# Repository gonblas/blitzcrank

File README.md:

# Blitzcrank

<p align="center">

</p>

## Descripción del proyecto

El proyecto **Blitzcrank** es un prototipo de **garra robótica móvil** diseñado para desplazarse en dos ejes (X e Y) mediante un sistema de rieles. Sobre este plano de movimiento, la garra puede **subir, bajar, abrir y cerrar**, lo que le otorga la capacidad de manipular objetos livianos dentro de un área determinada. El control se realiza manualmente a través de un **joystick de efecto Hall** y un conjunto de botones que permiten al usuario interactuar de manera sencilla e intuitiva.

Más allá de su valor como ejercicio técnico, el prototipo puede servir como base para múltiples aplicaciones: desde la simulación de procesos de **transporte y manipulación de piezas** hasta escenarios lúdicos como las clásicas máquinas de garras o sistemas recreativos de precisión, por ejemplo, un robot capaz de jugar al ajedrez moviendo las piezas en el tablero. De esta manera, Blitzcrank demuestra cómo la **tecnología robótica** puede adaptarse tanto a la **experimentación educativa** como a la **innovación aplicada** en proyectos más complejos.

<details>
  <summary><i>Objetivos del proyecto</i></summary>

  - **Objetivos primarios:**

    Se detallan a continuación aquellos objetivos de carácter obligatorio, necesarios para la validación del proyecto.

    - Implementar un sistema de rieles que permita el desplazamiento de la garra en los ejes X e Y.
    - Incorporar un mecanismo que posibilite el movimiento vertical de la garra para subir y bajar.
    - Desarrollar un sistema de control manual que garantice un manejo sencillo e intuitivo.
    - Integrar un actuador que permita abrir y cerrar la garra para tomar y soltar objetos.

  - **Objetivos secundarios:**

    A continuación se detallan aquellos objetivos de carácter opcional, sujetos a tiempo, materiales y costos disponibles.

    - Adaptar el sistema para manipular piezas de ajedrez en un tablero, garantizando precisión en la colocación.
    - Implementar un módulo de visión artificial que permita identificar la posición de las piezas en el tablero.
    - Integrar un algoritmo de inteligencia artificial que tome decisiones de juego y guíe automáticamente los movimientos de la garra.
    - Implementar una interfaz web que permita el manejo de la garra.

</details>

<details>
  <summary><i>Requerimientos del proyecto</i></summary>

  ##### Requerimientos Funcionales

  - **Requerimientos de Hardware:**

    - Debe contar con una interfaz física para mover la garra.
      - El sistema debe incluir unos botones dedicados al ascenso y descenso de la garra.
      - El sistema debe incluir un potenciómetro dedicado a la apertura y cierre de la garra.
      - El sistema debe incorporar un controlador para manejar los movimientos de la garra en los ejes X e Y.
      - El sistema debe incorporar un botón para manejar el cambio de modo físico y remoto.
    - Movimiento preciso de la garra.
      - El sistema de rieles debe permitir el movimiento de la garra en dos ejes cartesianos (X e Y), con un área mínima de trabajo de 15 cm x 15 cm.
      - El eje Z debe recorrer verticalmente al menos 5 cm para tomar y elevar piezas.
      - Se deben utilizar motores paso a paso para garantizar la posición exacta de la garra.
      - La garra debe ser capaz de levantar objetos de 50 gramos.
    - Todos los componentes deben estar ensamblados con fines de obtener un único sistema final compacto.

  - **Requerimientos de Software:**

    - Se debe desarrollar una interfaz de usuario capaz de controlar el sistema.
      - Desarrollar una interfaz que permita controlar manualmente la garra.
      - Implementar una interfaz web que permita seleccionar el modo de operación.
      - La interfaz debe ser intuitiva y clara, mostrando el estado del sistema y los errores en caso de que ocurran.
    - El software debe gestionar los límites de movimiento, deteniendo la garra para evitar daños mecánicos.

  ##### Requerimientos no funcionales

  Estos requerimientos no afectan en la funcionalidad del proyecto, por lo cual no se ve necesidad de hacer particular énfasis en la validación, pero que sí han sido tenidos en cuenta en el desarrollo.

  - Plataforma y desarrollo.
    - Utilizar una placa EDU-CIAA-NXP como centro de control del sistema, basada en el microcontrolador NXP LPC 4337.
    - Todo el firmware del EDU-CIAA debe ser desarrollado en lenguaje C.
  - Tiempo de ejecución: 16 semanas.
  - Presupuesto total de 600.000 ARS.
  - Documentación.
    - Documentar detalladamente el proceso de ensamblado del sistema.
    - Documentar el desarrollo del firmware, incluyendo rutinas de control e inicialización.
    - Documentar el diseño del esquemático y PCB, incluyendo conexiones, componentes y disposición de pines.
  - Garantizar la seguridad del usuario durante la operación del sistema, incluyendo protecciones físicas.

</details>

<details>
  <summary><i>Diagrama en bloques del sistema</i></summary>

</details>

<details>
  <summary><i>Tecnologías utilizadas</i></summary>
  <ol>

  <li>Hardware</li>
    <ul>
      <li>EDU-CIAA-NXP (LPC4337): placa central de control del sistema</li>
      <li>ESP-WROOM-32: módulo Wi-Fi para control remoto e interfaz web</li>
      <li>Motores paso a paso Nema17: movimiento en ejes X e Y</li>
      <li>Drivers DRV8825: control de motores paso a paso</li>
      <li>Motor DC GA12N20 + Driver DRV8833: accionamiento de polea</li>
      <li>Servomotor TowerPro MG90s: apertura y cierre de la garra</li>
      <li>Joystick analógico SYSPORT: control de movimiento X-Y</li>
      <li>Potenciómetro 10k: control analógico de la garra</li>
      <li>Fuente 12V 5A + Step Down XL4005: alimentación del sistema</li>
    </ul>

  <li>Firmware</li>
    <ul>
      <li>Lenguaje C para el firmware de la EDU-CIAA-NXP</li>
      <li>C++ con Arduino Framework para el firmware del ESP32</li>
      <li>PlatformIO como entorno de desarrollo del ESP32</li>
      <li>Comunicación UART entre EDU-CIAA y ESP32</li>
    </ul>

  <li>Interfaz web (ESP32)</li>
    <ul>
      <li>HTML, CSS y JavaScript servidos desde SPIFFS</li>
      <li>ESPAsyncWebServer para el servidor web embebido</li>
      <li>WebSockets para comunicación en tiempo real</li>
    </ul>

  <li>Diseño y fabricación</li>
    <ul>
      <li><a href="https://www.kicad.org/">KiCad</a>: diseño de esquemáticos y PCB</li>
      <li><a href="https://www.autodesk.com/products/fusion-360/overview">Fusion 360</a>: modelado 3D de estructura y garra</li>
      <li><a href="https://ultimaker.com/es/software/ultimaker-cura/">UltiMaker Cura</a>: preparación de piezas para impresión 3D</li>
    </ul>

  </ol>
</details>

---

## Materiales

| Componente | Cantidad | Función |
| ---------- | -------- | ------- |
| EDU-CIAA-NXP | 1 | Placa central que coordina motores, sensores y comunicación |
| ESP-WROOM-32 38 PINES | 1 | Control inalámbrico mediante Wi-Fi, interfaz web remota |
| Potenciómetro 10k Lineal 16mm | 1 | Entrada analógica para apertura de garra |
| Push Button Tact Switch 6x6mm | 3 | Entrada digital para abrir/cerrar garra |
| Joystick analógico SYSPORT | 1 | Control principal en ejes X e Y con pulsador integrado |
| Motor DC GA12N20 | 1 | Motorreductor para accionar polea |
| Driver Motor DC Puente H DRV8833 | 1 | Control de motor DC, inversión de giro y regulación por PWM |
| Servomotor TowerPro MG90s | 1 | Apertura y cierre de la garra |
| Motor paso a paso Nema17 17HS3404N | 2 | Movimiento de ejes X-Y |
| Driver DRV8825 | 2 | Controlador de motores paso a paso |
| Fuente de 12V 5A SIMALED LCS-1721-M1 | 1 | Fuente de alimentación externa para todo el sistema |
| Módulo Step Down XL4005 | 1 | Transformador de tensión |

---

## Diseño 3D

<details>
  <summary>Sistema completo</summary>
  
</details>

<details>
  <summary>Garra</summary>
  
</details>

<details>
  <summary>Sistema de poleas</summary>
  
</details>

<details>
  <summary>Controlador</summary>

</details>

<details>
  <summary>Eje Y</summary>
  
</details>

---

## PCB

<details>
  <summary>Diseño del PCB</summary>
  
</details>

<details>
  <summary>PCB 3D</summary>
  
</details>

<details>
  <summary>PCB Construído</summary>
  
</details>

---

## Estructura del Proyecto

```
Blitzcrank/
│
├── build/                        # Archivos de compilación
├── docs/                         # Documentación y diagramas del proyecto
├── firmware/                     # Directorio principal del firmware
│   ├── mainboard/                # Firmware del controlador principal (LPC4337)
│   │   ├── .settings/            # Configuración del entorno de desarrollo
│   │   ├── app/                  # Aplicación principal del firmware
│   │   │   ├── drivers/          # Drivers de hardware (UART, SPI, I2C, GPIO, etc.)
│   │   │   ├── inc/              # Archivos de encabezado propios del proyecto
│   │   │   ├── out/              # Archivos de salida (build temporal, objetos, etc.)
│   │   │   └── src/              # Código fuente de la aplicación
│   │   │       └── main.c        # Punto de entrada del firmware
│   │   │
│   │   ├── examples/             # Ejemplos de uso de las distintas librerías
│   │   ├── libs/                 # Librerías externas o módulos reutilizables
│   │   ├── scripts/              # Scripts auxiliares para automatizar tareas del proyecto
│   │   ├── test/                 # Código de pruebas del hardware y validación de módulos
│   │   ├── .cproject             # Configuración del compilador (Eclipse)
│   │   ├── .gitignore            # Archivos ignorados por Git
│   │   ├── .project              # Configuración del proyecto (Eclipse)
│   │   ├── .travis.yml           # Integración continua (Travis CI)
│   │   ├── board.mk              # Configuración específica de la placa (paths, flags, etc.)
│   │   ├── LICENSE               # Licencia del proyecto
│   │   ├── Makefile              # Archivo principal de construcción del proyecto
│   │   ├── program.mk            # Reglas de programación/flasheo del firmware
│   │   ├── README.md             # Documentación general del firmware principal
│   │
│   └── esp-32/                   # Firmware del módulo ESP32
│       ├── src/                  # Código fuente principal (main.cpp)
│       │
│       ├── lib/                  # Librerías locales del proyecto
│       │   ├── WiFiManager/      # Manejo de conexión Wi-Fi y modo AP
│       │   ├── SpiffsManager/    # Gestión del sistema de archivos SPIFFS (lectura/escritura)
│       │   ├── Routes/           # Ruteo de peticiones HTTP y manejo del servidor web
│       │   └── UARTManager/      # Comunicación serial UART y sincronización de datos con la web
│       │
│       ├── data/                 # Archivos de la interfaz web que se suben al SPIFFS
│       │   ├── index.html
│       │   ├── style.css
│       │   └── script.js
│       │
│       ├── include/  
│       ├── lib/                  # Librerías externas (ESPAsyncWebServer, etc.)
│       ├── platformio.ini        # Configuración de PlatformIO
│       └── test/                 # Pruebas específicas del ESP
│
├── hardware/                     # Diseños de PCB, Esquemáticos, Diseños 3D
│   ├── pcb/                      # Diseños de PCB
│   ├── 3d-design/                # Diseños 3D
│   └── schematic/                # Circuitos esquemáticos
│
├── resources/                    # Documentación técnica y de apoyo
│   ├── 3d-design/                # Imágenes de los diseños 3D
│   ├── datasheets/               # Datasheets de los componentes utilizados
│   ├── manuals/                  # Manuales de módulos, sensores, devkits, etc.
│   ├── notes/                    # Apuntes técnicos, application notes, cálculos útiles
│   └── schematics/               # Esquemas de conexión, wiring y diagramas eléctricos
│
├── .clang-format                 # Configuración de estilo de código
├── .gitignore                    # Archivos ignorados por Git
├── LICENSE                       # Licencia del proyecto
├── README.md                     # Archivo actual
└── STYLE_GUIDE.md                # Convenciones de estilo del proyecto
```

Para ver las convenciones de nombres y estilo de código, consultar [STYLE_GUIDE.md](./STYLE_GUIDE.md)

---

## Flujo de funcionamiento del sistema

<p align="center">
  
</p>

<p align="center">

</p>

---

## Autores

<ul>
  <li>

    <strong>Blasco, Gonzalo</strong>
    <br clear="right"/>
  </li>

  <li>

    <strong>Polanis, Iván Valentín</strong>
    <br clear="right"/>
  </li>

  <li>

    <strong>Romero, Mateo</strong>
    <br clear="right"/>
  </li>

  <li>

    <strong>Savenia, Manuel</strong>
    <br clear="right"/>
  </li>
</ul>

## Coordinador

<ul>
  <li>

    <strong>Joaquín Chanquía</strong><br />
    <em>Ayudante – Taller de Proyecto I</em>
    <br clear="right"/>
  </li>
</ul>

---

## Licencia

Este proyecto se distribuye bajo la licencia [GPL](LICENSE).

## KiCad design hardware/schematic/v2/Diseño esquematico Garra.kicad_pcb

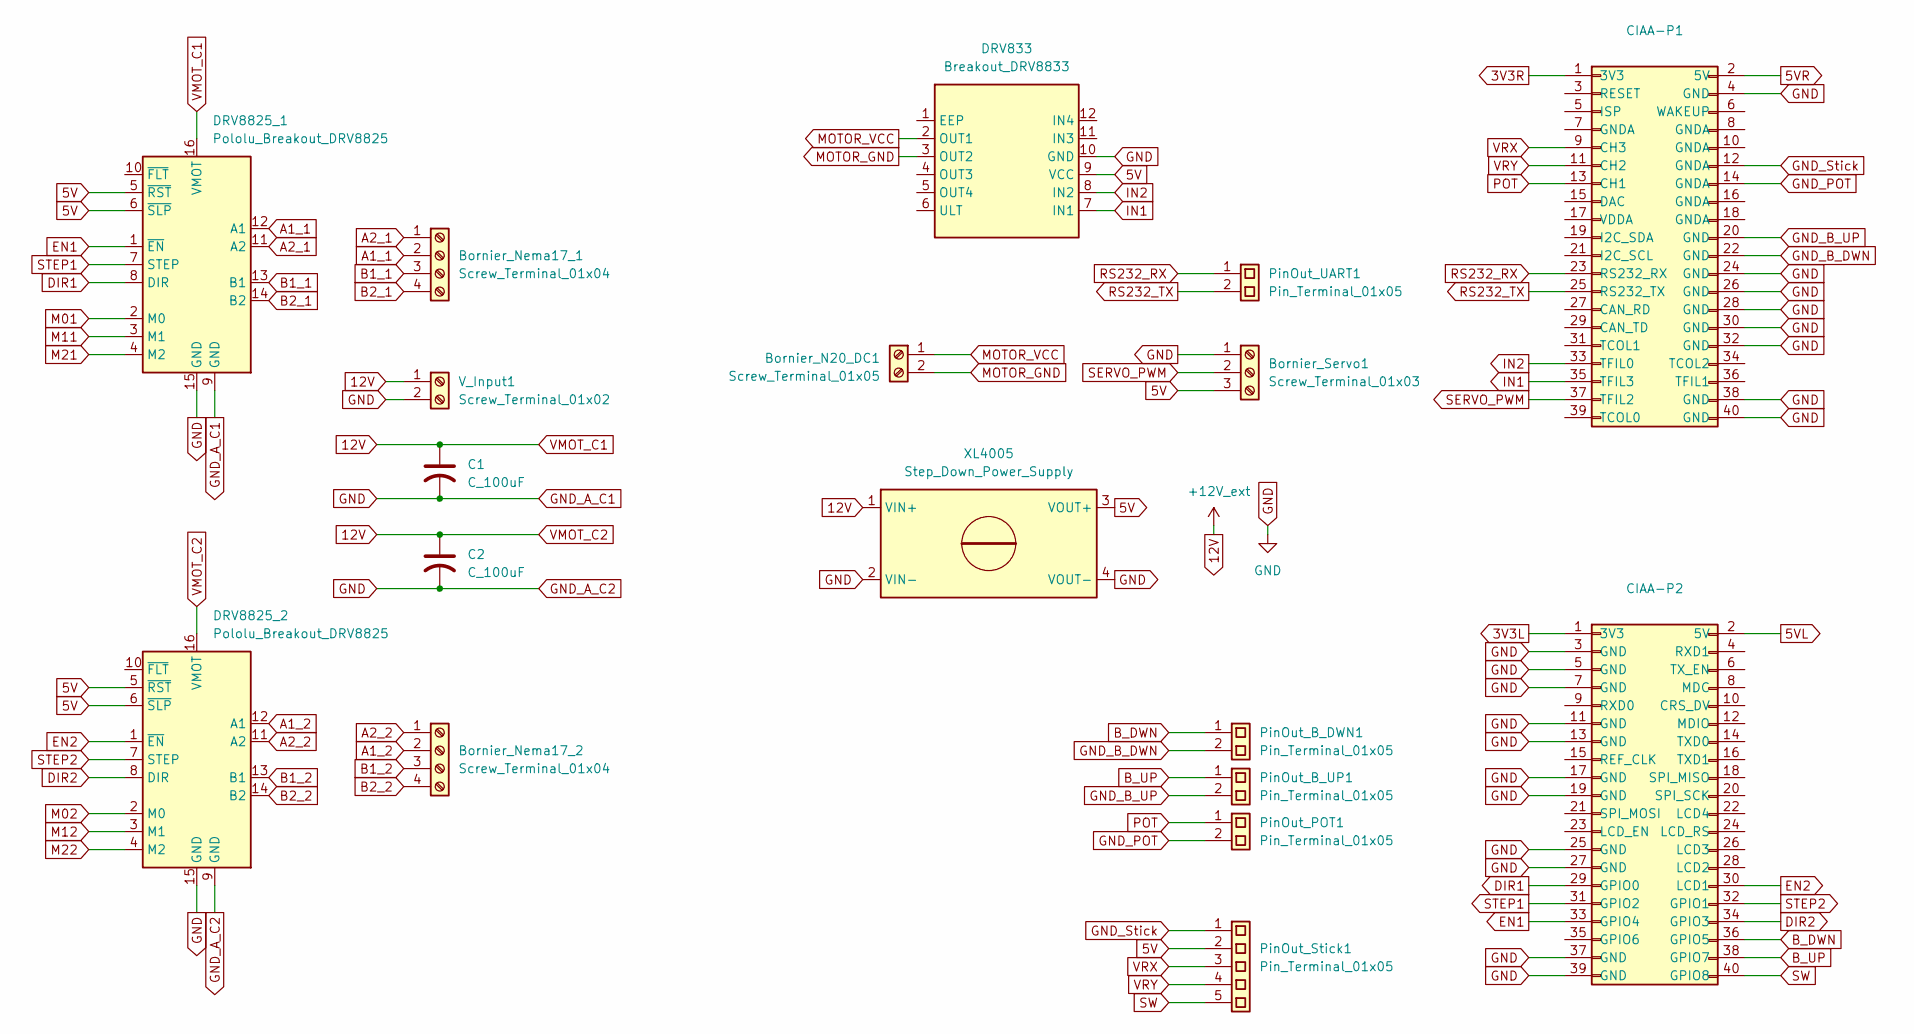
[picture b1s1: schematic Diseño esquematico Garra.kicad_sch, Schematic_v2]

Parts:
Bornier_N20_DC1: Screw_Terminal_01x05; TerminalBlock_Phoenix_MKDS-1,5-2-5.08_1x02_P5.08mm_Horizont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
Bornier_Nema17_1, Bornier_Nema17_2: Screw_Terminal_01x04; TerminalBlock_Phoenix_MKDS-1,5-4-5.08_1x04_P5.08mm_Horizont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
Bornier_Servo1: Screw_Terminal_01x03; TerminalBlock_Phoenix_MKDS-1,5-3-5.08_1x03_P5.08mm_Horizont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
C1, C2: C_100uF; C_Radial_D8.0mm_H11.5mm_P3.50mm
CIAA-P1, CIAA-P2: PIN_ARRAY_20X2
DRV833: Breakout_DRV8833; Pololu_Breakout-16_15.2x20.3mm
DRV8825_1, DRV8825_2: Pololu_Breakout_DRV8825; Pololu_Breakout-16_15.2x20.3mm
PinOut_B_DWN1: Pin_Terminal_01x05; PinSocket_1x02_P2.00mm_Vertical
PinOut_B_UP1: Pin_Terminal_01x05; PinSocket_1x02_P2.00mm_Vertical
PinOut_POT1: Pin_Terminal_01x05; PinSocket_1x02_P2.00mm_Vertical
PinOut_Stick1: Pin_Terminal_01x05; PinSocket_1x05_P2.00mm_Vertical
PinOut_UART1: Pin_Terminal_01x05; PinSocket_1x02_P2.00mm_Vertical
V_Input1: Screw_Terminal_01x02; TerminalBlock_Phoenix_MKDS-1,5-2-5.08_1x02_P5.08mm_Horizont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
XL4005: Step_Down_Power_Supply; Pololu_Breakout-16_15.2x20.3mm

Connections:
3V3L: CIAA-P2.1 (3V3)
3V3R: CIAA-P1.1 (3V3)
5V: Bornier_Servo1.3, DRV833.9 (VCC), DRV8825_1.5 (~RST), DRV8825_1.6 (~SLP), DRV8825_2.5 (~RST), DRV8825_2.6 (~SLP), PinOut_Stick1.2, XL4005.3 (VOUT+)
5VL: CIAA-P2.2 (5V)
5VR: CIAA-P1.2 (5V)
12V: C1.1, C2.1, DRV8825_1.16 (VMOT), DRV8825_2.16 (VMOT), V_Input1.1, XL4005.1 (VIN+)
A1_1: Bornier_Nema17_1.2, DRV8825_1.12 (A1)
A1_2: Bornier_Nema17_2.2, DRV8825_2.12 (A1)
A2_1: Bornier_Nema17_1.1, DRV8825_1.11 (A2)
A2_2: Bornier_Nema17_2.1, DRV8825_2.11 (A2)
B1_1: Bornier_Nema17_1.3, DRV8825_1.13 (B1)
B1_2: Bornier_Nema17_2.3, DRV8825_2.13 (B1)
B2_1: Bornier_Nema17_1.4, DRV8825_1.14 (B2)
B2_2: Bornier_Nema17_2.4, DRV8825_2.14 (B2)
B_DWN: CIAA-P2.36 (GPIO5), PinOut_B_DWN1.1
B_UP: CIAA-P2.38 (GPIO7), PinOut_B_UP1.1
DIR1: CIAA-P2.29 (GPIO0), DRV8825_1.8 (DIR)
DIR2: CIAA-P2.34 (GPIO3), DRV8825_2.8 (DIR)
EN1: CIAA-P2.33 (GPIO4), DRV8825_1.1 (~EN)
EN2: CIAA-P2.30 (LCD1), DRV8825_2.1 (~EN)
GND: Bornier_Servo1.1, C1.2, C2.2, CIAA-P1.4 (GND), CIAA-P1.24 (GND), CIAA-P1.26 (GND), CIAA-P1.28 (GND), CIAA-P1.30 (GND), CIAA-P1.32 (GND), CIAA-P1.38 (GND), CIAA-P1.40 (GND), CIAA-P2.3 (GND), CIAA-P2.5 (GND), CIAA-P2.7 (GND), CIAA-P2.11 (GND), CIAA-P2.13 (GND), CIAA-P2.17 (GND), CIAA-P2.19 (GND), CIAA-P2.25 (GND), CIAA-P2.27 (GND), CIAA-P2.37 (GND), CIAA-P2.39 (GND), DRV833.10 (GND), DRV8825_1.9 (GND), DRV8825_1.15 (GND), DRV8825_2.9 (GND), DRV8825_2.15 (GND), V_Input1.2, XL4005.2 (VIN-), XL4005.4 (VOUT-)
GND_B_DWN: CIAA-P1.22 (GND), PinOut_B_DWN1.2
GND_B_UP: CIAA-P1.20 (GND), PinOut_B_UP1.2
GND_POT: CIAA-P1.14 (GNDA), PinOut_POT1.2
GND_Stick: CIAA-P1.12 (GNDA), PinOut_Stick1.1
IN1: CIAA-P1.35 (TFIL3), DRV833.7 (IN1)
IN2: CIAA-P1.33 (TFIL0), DRV833.8 (IN2)
M01: DRV8825_1.2 (M0)
M02: DRV8825_2.2 (M0)
M11: DRV8825_1.3 (M1)
M12: DRV8825_2.3 (M1)
M21: DRV8825_1.4 (M2)
M22: DRV8825_2.4 (M2)
MOTOR_GND: Bornier_N20_DC1.2, DRV833.3 (OUT2)
MOTOR_VCC: Bornier_N20_DC1.1, DRV833.2 (OUT1)
POT: CIAA-P1.13 (CH1), PinOut_POT1.1
RS232_RX: CIAA-P1.23 (RS232_RX), PinOut_UART1.1
RS232_TX: CIAA-P1.25 (RS232_TX), PinOut_UART1.2
SERVO_PWM: Bornier_Servo1.2, CIAA-P1.37 (TFIL2)
STEP1: CIAA-P2.31 (GPIO2), DRV8825_1.7 (STEP)
STEP2: CIAA-P2.32 (GPIO1), DRV8825_2.7 (STEP)
SW: CIAA-P2.40 (GPIO8), PinOut_Stick1.5
VRX: CIAA-P1.9 (CH3), PinOut_Stick1.3
VRY: CIAA-P1.11 (CH2), PinOut_Stick1.4

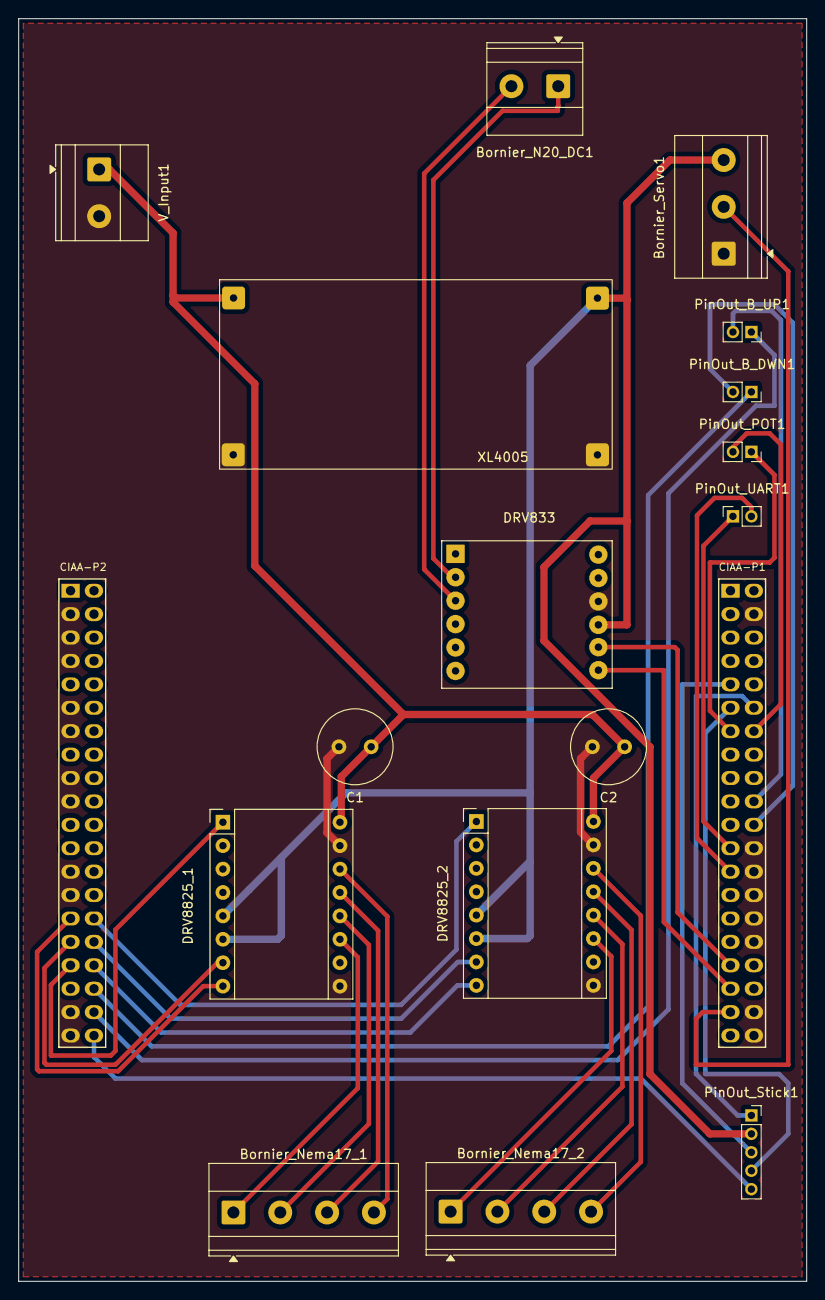
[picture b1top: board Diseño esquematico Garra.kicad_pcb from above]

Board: 2 copper layers, 85.5 x 137.0 mm, 18 parts (0 on the bottom side), 34 nets.

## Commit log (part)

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2025-09-18 EDU-CIAA Schematics/PCB Kicad
2025-09-22 New Kicad scheme
2025-09-25 style: Refactor code structure for improved readability and maintainability
2025-09-25 Fixes to Schematic
2025-09-29 Schematics updated + PCB
2025-09-29 feat: add docs
2025-09-29 schematic update
2025-09-30 Added buttons/potentimeter to schematics
2025-10-01 feat: replace driver DDRV8833 for BTS7960
2025-10-01 schematics plot updated
2025-10-01 Schematics updated - borniers,pins
2025-10-02 chore: change schematic v1 name
2025-10-02 Fixing merge conflicts
2025-10-02 Added 3d-designs
2025-10-02 Schematics updated - Step down PS & capacitor
2025-10-05 Added all stl files for 3d printing
2025-10-05 style: enhance directory naming
2025-10-07 Schematics updated
2025-10-09 PCB started
2025-10-09 PCB progress
2025-10-11 feat: Add platform configuration for ESP32 in PlatformIO
2025-10-13 feat: Implemented a new main.c file with two LED tasks that toggle LED1 and LED2 at different intervals with a RTOS approach
2025-10-13 PCB Updated
2025-10-14 feat: Add Wi-Fi connectivity and web server functionality with HTML control interface to esp32
2025-10-14 feat: Implement hold functionality for button actions in script.js
2025-10-14 feat: Update project structure in README.md for improved clarity and organization
2025-10-14 Esp32 webpage (#1)
    * feat: Add Wi-Fi connectivity and web server functionality with HTML control interface to esp32
    * feat: Refactor Wi-Fi connectivity and web server implementation with new HTML/CSS interface
    * feat: Implement hold functionality for button actions in script.js
    * feat: Refactor Wi-Fi connectivity and SPIFFS management with new routing structure
    * feat: Update project structure in README.md for improved clarity and organization
2025-10-15 Add initial FreeRTOS configuration and example tasks for LED control
    - Created launch configuration for PlatformIO debugging in esp-32 firmware.
    - Added config.mk for build options and library usage in mainboard application.
    - Included FreeRTOSConfig.h with standard configurations for FreeRTOS.
    - Defined main.h with basic structure for the main application.
    - Implemented main.c with two tasks to toggle LEDs at different intervals.
2025-10-15 feat: PCB routing first stage completed
2025-10-15 feat: add hardware testing for joystick, pot and buttons
2025-10-15 fix: PCB border colision
2025-10-16 feat: implement servo control with PWM mapping and add initial task files
2025-10-17 feat: add initial implementation for joystick and potentiometer control tasks
2025-10-17 feat: add how joystick 2-axis works
2025-10-17 feat: add favicon and enhance hold indicator styles with animations
2025-10-17 feat: disable controls on initial load for improved user experience
2025-10-17 feat(uart): add UART communication with EDU-CIAA feat(web): enhance web accessibility and control feedback (#2)
    * feat: Add Wi-Fi connectivity and web server functionality with HTML control interface to esp32
    * feat: Refactor Wi-Fi connectivity and web server implementation with new HTML/CSS interface
    * feat: Implement hold functionality for button actions in script.js
    * feat: Refactor Wi-Fi connectivity and SPIFFS management with new routing structure
    * feat: Update project structure in README.md for improved clarity and organization
    * feat: Add mode switch for web control and update control states in UI
2025-10-17 feat: refactor control system with joystick, buttons, and potentiometer integration
2025-10-17 feat: enhance control logic with switch and LED state management
2025-10-17 refactor: remove unused joystick control code and update stylesheet/script paths in index.html
2025-10-17 fix: add .vscode to .gitignore to prevent tracking of IDE configuration files
2025-10-18 feat: implement control tasks for gripper, XY, and Z axes with event system integration
2025-10-18 feat: enhance task management and event handling with improved debugging and structure
2025-10-18 feat: define heap sizes and task priorities for control tasks
2025-10-19 feat: add stepper task and integrate joystick event handling
2025-10-19 feat: implement conditional debug logging system across tasks and main application
2025-10-19 Mainboard firmware (#4)
    * feat: implement control tasks for gripper, XY, and Z axes with event system integration
    * feat: enhance task management and event handling with improved debugging and structure
    * feat: add task handles for control tasks and enhance switch mode task functionality
    * feat: define heap sizes and task priorities for control tasks
    * feat: implement servo task and related utilities for improved control
    * feat: add stepper task and integrate joystick event handling
2025-10-19 feat: update UI controls and styles for joystick and gripper, adjust Wi-Fi configuration
2025-10-20 feat: add through holes for connectivity & GNDs links
2025-10-20 feat: implement input source mode handling and update related protocols
2025-10-20 feat: add UART communication functions and refactor mode switching logic
2025-10-20 feat: implement WebSocket communication for input source mode changes and refactor related components
2025-10-21 feat: refactor event handling and add queue functions for joystick, button, potentiometer, and input source events
2025-10-21 feat: implement controls state management and mode switching functionality
    Authored-by: Iván Valentín Polanis <ivanpolanis@users.noreply.github.com>
2025-10-21 Squashed commit of the following:
    commit 0431c74edf3d14fb2bf3e3c5d96064db9f72ee8f
    Author: Iván Valentín Polanis <51934556+ivanpolanis@users.noreply.github.com>
    Date: Sun Oct 19 12:04:46 2025 -0300
    Mainboard firmware (#4)
    * feat: implement control tasks for gripper, XY, and Z axes with event system integration
    * feat: enhance task management and event handling with improved debugging and structure
2025-10-21 Mainboard firmware (#6)
    * feat: implement control tasks for gripper, XY, and Z axes with event system integration
    * feat: enhance task management and event handling with improved debugging and structure
    * feat: add task handles for control tasks and enhance switch mode task functionality
    * feat: define heap sizes and task priorities for control tasks
    * feat: implement servo task and related utilities for improved control
    * feat: add stepper task and integrate joystick event handling
2025-10-23 feat: hole diameter adjustment
2025-10-23 fix: PDF
2025-10-23 docs: Added Render files for modified pieces
2025-10-24 feat: added controller disconnect safety task
2025-10-25 feat: Made Corrections to claw mechanism to improve the performance of the gears
2025-10-25 feat: implement code functionality to steppers
2025-10-26 feat: increased hole sizes for claw pieces to reduce friction
2025-10-27 feat: change route system in PCB
2025-10-27 feat: improved fitting of the gears. Modified controller bottom to include holes for perfboard
2025-10-28 feat: add new test and final functionality integration to main task
2025-10-28 feat: add reports
2025-10-28 Pcb branch (#8)
    * refactor
    * feat: PCB routing first stage completed
    * docs: Schematics PDF added
    * fix: PCB border colision
    * feat: Copper layers added to the PCB
    * feat: New PCB design with new components [LED, B_M]
2025-10-29 feat: add new esp32 schematic
2025-10-30 feat: take png and pdf from finished schematic
2025-10-30 feat: valid pdf PCB template
2025-10-31 feat: added render images for modified pieces
2025-11-02 feat: add render image inside controller
2025-11-02 Rename 20190130071429_7826.pdf to NEMA17.pdf
2025-11-02 feat: add GA12-N20 datasheet
2025-11-02 docs: modify render image inside controller for better contrast
2025-11-02 feat: add DC motor control functionality and configuration
2025-11-03 fix: swap GPIO pins for button and joystick functionality
2025-11-03 fix: Expand PCB routes and copper holes
2025-11-03 feat: update status text for web control and enhance disabled slider styles
2025-11-11 feat: Change PCB design and clearance
2025-11-13 feat: update controller connection handling and logging format
2025-11-13 feat: initialize global state and add VSCode settings for file associations
2025-11-13 feat: update button pin definition and clean joystick code
2025-11-14 feat: Change Stick_on from ISP to CAN_RD
2025-11-17 feat: increase hole diameter for PinOuts
2025-12-01 Esp32 (#15)
    * feat: Add Wi-Fi connectivity and web server functionality with HTML control interface to esp32
    * feat: Refactor Wi-Fi connectivity and web server implementation with new HTML/CSS interface
    * feat: Implement hold functionality for button actions in script.js
    * feat: Refactor Wi-Fi connectivity and SPIFFS management with new routing structure
    * feat: Update project structure in README.md for improved clarity and organization
    * feat: Add mode switch for web control and update control states in UI
2025-12-05 docs: fix error in RJ-45 Pinout
2025-12-06 Revert "Esp32 (#15)"
    This reverts commit bf51cb744312f9b626049e7e4bf70f72b9cf64da.
2025-12-06 Revert "Esp32 (#15)" (#17)
    This reverts commit bf51cb744312f9b626049e7e4bf70f72b9cf64da.
2025-12-06 feat: improve Wi-Fi connection handling and add watchdog functionality
2025-12-06 feat: update potentiometer handling to improve value mapping and processing
2025-12-06 feat: update control gripper task to track potentiometer angle in global state
2025-12-08 feat: enhance logging system and update Wi-Fi configuration
2025-12-08 feat: implement joystick data throttling and improve server communication
2025-12-08 feat: update controlGripperTask to use defined min/max potentiometer values for scaling
2025-12-08 feat: enhance UART task with improved frame validation and detailed logging
2025-12-08 feat: correct joystick axis reading order in controlXYAxisTask and use defined UART_BAUD in UART_TaskCreate
2025-12-14 Mainboard (#18)
    * feat: add debug prints for UART frame validation and connection state
    * feat: update control gripper task to track potentiometer angle in global state
    * feat: increase DEAD_ZONE value to improve joystick sensitivity handling
    * feat: update controlGripperTask to use defined min/max potentiometer values for scaling
    * feat: enhance UART task with improved frame validation and detailed logging
    * feat: correct joystick axis reading order in controlXYAxisTask and use defined UART_BAUD in UART_TaskCreate
2025-12-14 fix: correct potentiometer angle mapping
2025-12-23 doc: add Schematic 2.2V svg
2026-02-02 fix: refine angle scaling in controlGripperTask
2026-02-02 servo deadband update
2026-02-06 fix: update RJ-45 pinout table to include PONCHO pin assignments
2026-02-06 feat: implement rate limiting for joystick and potentiometer sends
2026-02-08 feat: refactor task constants and improve joystick/potentiometer handling
2026-02-08 feat: add axis state management and update Z motor control logic
2026-02-09 fix: change ESP32 I/O pins
2026-02-09 feat: change servo
2026-02-09 Refactor code structure for improved readability and maintainability
2026-02-13 feat: Refactor readme and add reports
2026-02-13 Update README with additional diagrams and images
    Added images and details for system block diagram and PCB.
